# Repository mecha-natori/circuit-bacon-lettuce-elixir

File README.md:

# Bacon Lettuce Elixir

Bacon Lettuce ElixirはESP32-C3-WROOM-02を使用したBluetooth-USB変換基板です。

USB Type-Aのポートにそのまま差せるため、書き込み・給電が容易です。

## 仕様

|        機能         | 個数 | 備考                                 |
| :-----------------: | ---: | :----------------------------------- |
|         MCU         |    1 | ESP32-C3-WROOM-02                    |
|        UART         |    1 | 電源ピンは5V・外部通信モジュール向け |
|   USB Type-A メス   |    1 | コントローラー接続用                 |
|   USB Type-A オス   |    1 | 給電・書き込み用                     |
|      Bluetooth      |    1 | MCU内蔵、Bluetooth 5 **(BLEのみ)**   |
|  リセットスイッチ   |    1 |                                      |
| 5V-3.3Vレギュレータ |    1 | 外部電源からの供給用                 |
|        寸法         |      | 30mm x 50mm                          |

## 名前の由来

BLTからトマトが消えてエリクサーになったとさ。 **B**luetooth **L**ow **E**nergyです。

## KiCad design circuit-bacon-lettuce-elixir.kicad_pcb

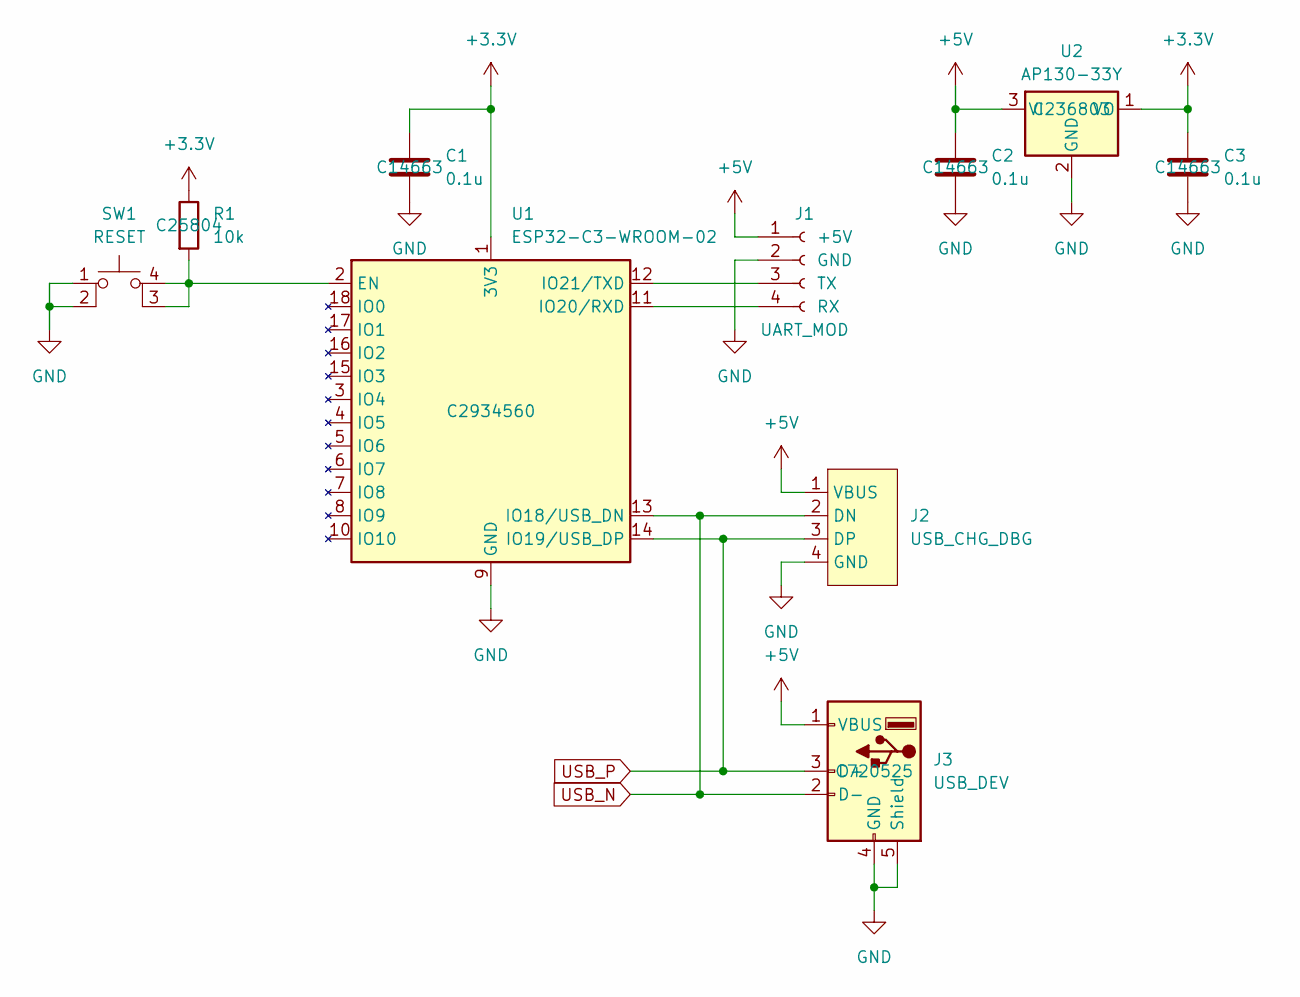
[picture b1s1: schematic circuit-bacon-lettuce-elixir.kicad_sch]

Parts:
C1, C2, C3: 0.1u; C_0603_1608Metric_Pad1.08x0.95mm_HandSolder; LCSC PN C14663
J1: UART_MOD; DF1B-4P-2.5DSA
J2: USB_CHG_DBG; PCB_USB_Connecter
J3: USB_DEV; USB_A_Receptacle_GCT_USB1046; LCSC PN C720525
R1: 10k; R_0603_1608Metric_Pad0.98x0.95mm_HandSolder; LCSC PN C25804
SW1: RESET; tact
U1: ESP32-C3-WROOM-02; LCSC PN C2934560
U2: AP130-33Y; SOT-89-3; LCSC PN C236803

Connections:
+3.3V: C1.1, C3.1, R1.1, U1.1 (3V3), U2.1 (VO)
+5V: C2.1, J1.1 (+5V), J2.1 (VBUS), J3.1 (VBUS), U2.3 (VI)
GND: C1.2, C2.2, C3.2, J1.2 (GND), J2.4 (GND), J3.4 (GND), J3.5 (Shield), SW1.1, SW1.2, U1.9 (GND), U1.19 (GND), U2.2 (GND)
unnamed: J1.4 (RX), U1.11 (IO20/RXD)
unnamed: J1.3 (TX), U1.12 (IO21/TXD)
unnamed: R1.2, SW1.3 (K), SW1.4 (A), U1.2 (EN)
USB_N: J2.2 (DN), J3.2 (D-), U1.13 (IO18/USB_DN)
USB_P: J2.3 (DP), J3.3 (D+), U1.14 (IO19/USB_DP)

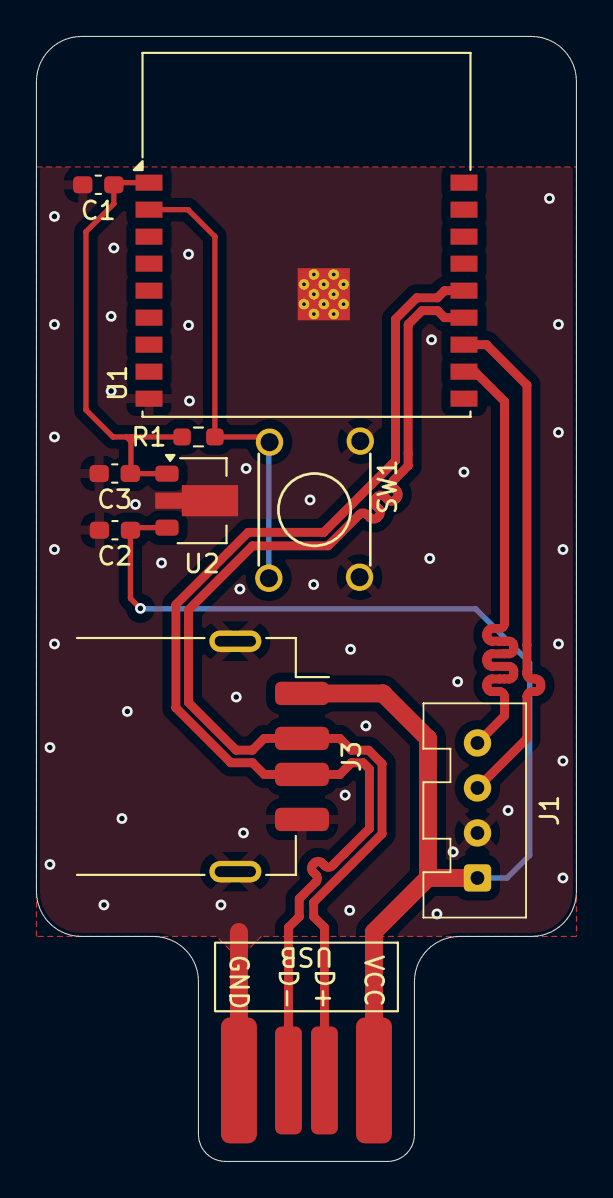
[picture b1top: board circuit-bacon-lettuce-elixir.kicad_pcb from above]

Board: 2 copper layers, 30.0 x 62.5 mm, 10 parts (0 on the bottom side), 8 nets.

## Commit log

2025-04-03 feature: ロゴ・リポジトリURLを追加。
2025-04-04 feature: 書き込み・給電コネクタをType-CからType-Aへ変更。
